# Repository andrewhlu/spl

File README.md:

<div class="center">
    
</div>

# Smart Parking Lot

A project for [ECE 189 - Computer Engineering Capstone](https://web.ece.ucsb.edu/~yoga/capstone/) led by Professor Isukapalli at UC Santa Barbara

---

[Parkingbase Demo Video](https://www.youtube.com/watch?v=abxjF7t0qpM)

[Parkingbase Poster](docs/poster.pdf)

---

## Team Members

* Andrew Lu
* Finn Linderman
* Luyao Han
* Seungjun Cho

## The Problem

Drivers spend too much time in parking lots trying to find an open space to park in. Many parking lots only have per-floor capacity indicators, and existing solutions are prohibitively expensive.

What if we could utilize low-cost sensors and a companion application to navigate drivers to empty parking spots faster, at a low cost to facility owners?

## Project Overview

**The goal of this project is to design a smart parking lot that will direct drivers to the nearest open parking space in an efficient, accurate, and clean manner.**

We accomplish this using:

* Small, inexpensive parking lot sensors with long-range and low-power transmission
* Modern, open-source, and cloud-based software solutions
* Easy-to-use mobile interfaces

# Technical Details

For a more detailed description, please take a look at our [project presentation slides](docs/final-presentation.pdf).

## System Overview

## Application Scene

## Block Diagram

<div class="center">
  
</div>

## Sensor Unit Assembly

<div class="center">

</div>

## Firmware Block Diagram

<div class="center">
  
</div>

## Sensor Unit PCB Design

The raw Kicad design files can be found in the [pcb-design folder](https://github.com/andrewhlu/spl/tree/main/pcb_design) in our repo.

[PCB Schematic (as PDF)](docs/sch.pdf)

[PCB Schematic (as PNG Image)](docs/sch.png)

## GUI Screenshots

Driver User Interface:

Editor User Interface:

## Code Repositories

* [spl](https://github.com/andrewhlu/spl)
  * Documentation for this website
  * PCB Design files
  * Demo pictures
* [spl-web](https://github.com/andrewhlu/spl-web)
  * Code for our website, including the React frontend and backend API routes
* [parkingbase-auth](https://github.com/andrewhlu/parkingbase-auth)
  * Code for our custom authentication server

# Project Progress Updates

[Initial Design](docs/initial-design.pdf)

[Milestone 1](docs/milestone1.pdf)

[Milestone 2](docs/milestone2.pdf)

[Fall Quarter Review Presentation](docs/fall-quarter-review.pdf)

[Winter Quarter Review Presentation](docs/winter-quarter-review.pdf)

[Final Poster](docs/poster.pdf)

[Final Presentation](docs/final-presentation.pdf)

<!-- Custom CSS for GitHub Pages -->

<style>
  .markdown-body h1:first-of-type {
    display: none;
  }

  .center {
    text-align: center;
    padding: 1rem;
  }
</style>

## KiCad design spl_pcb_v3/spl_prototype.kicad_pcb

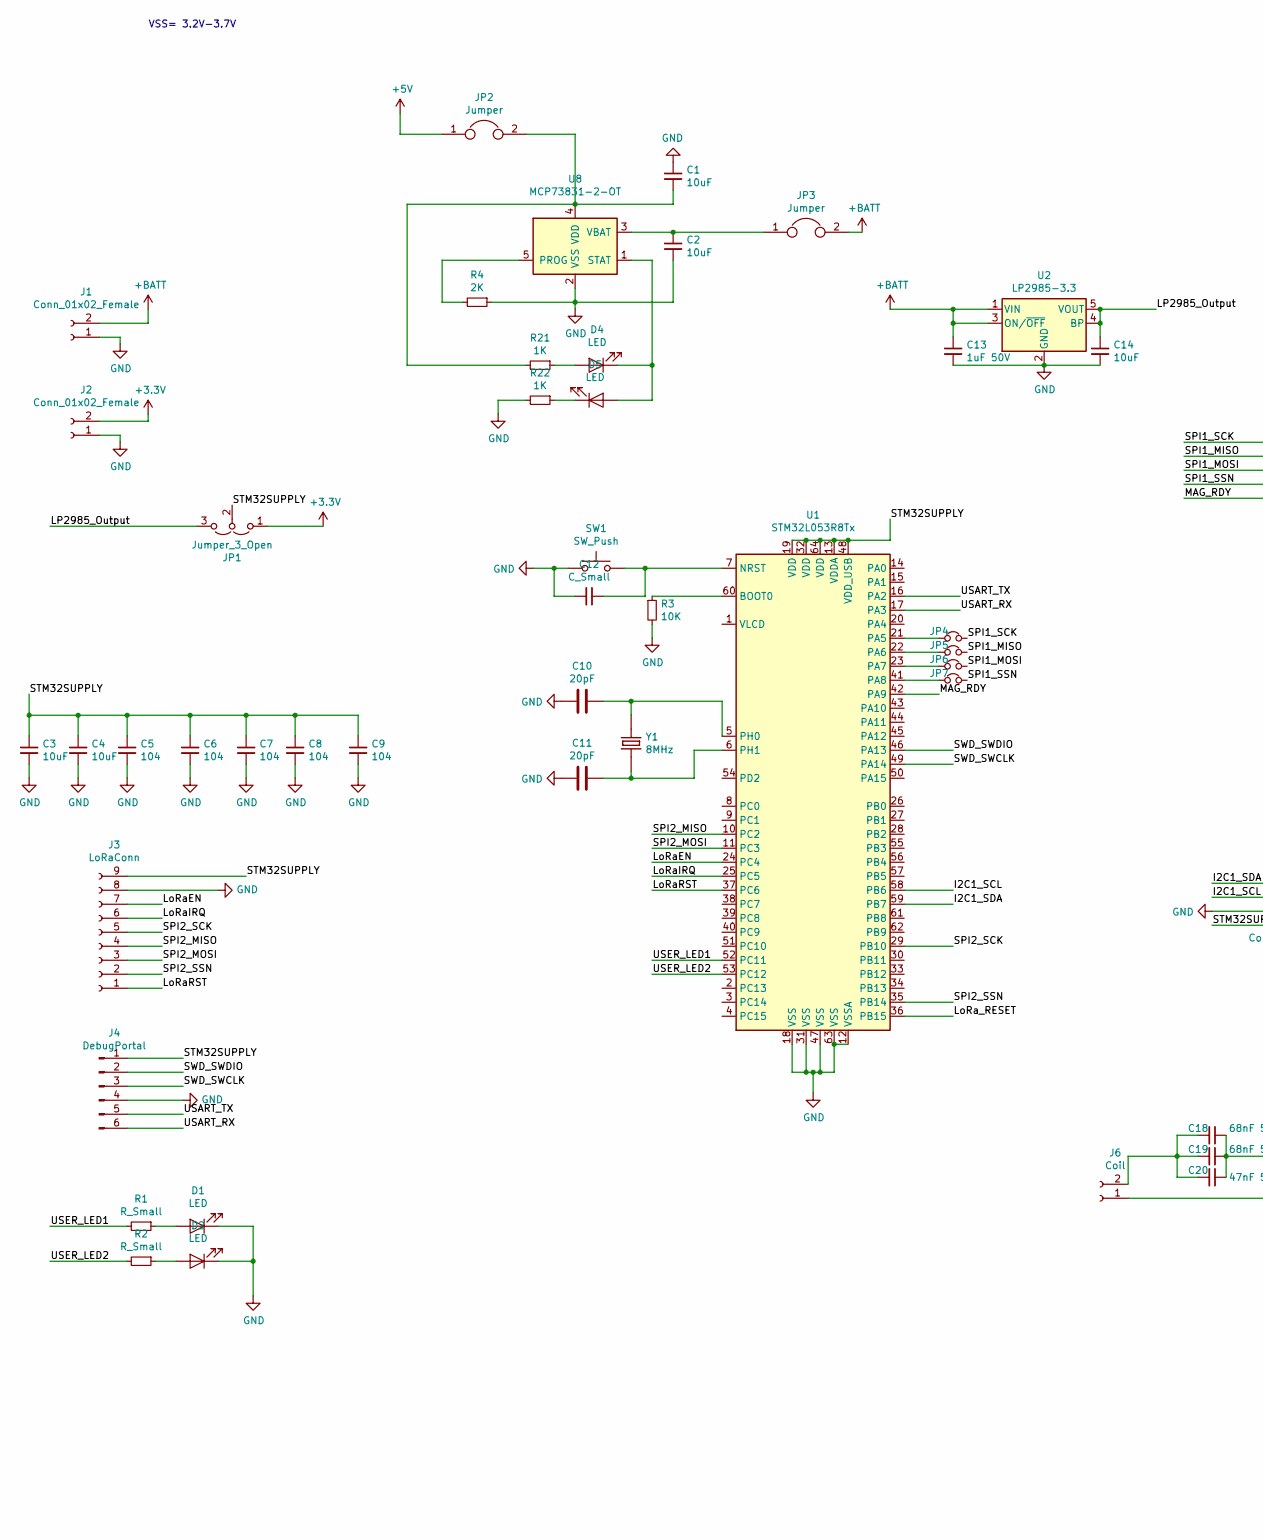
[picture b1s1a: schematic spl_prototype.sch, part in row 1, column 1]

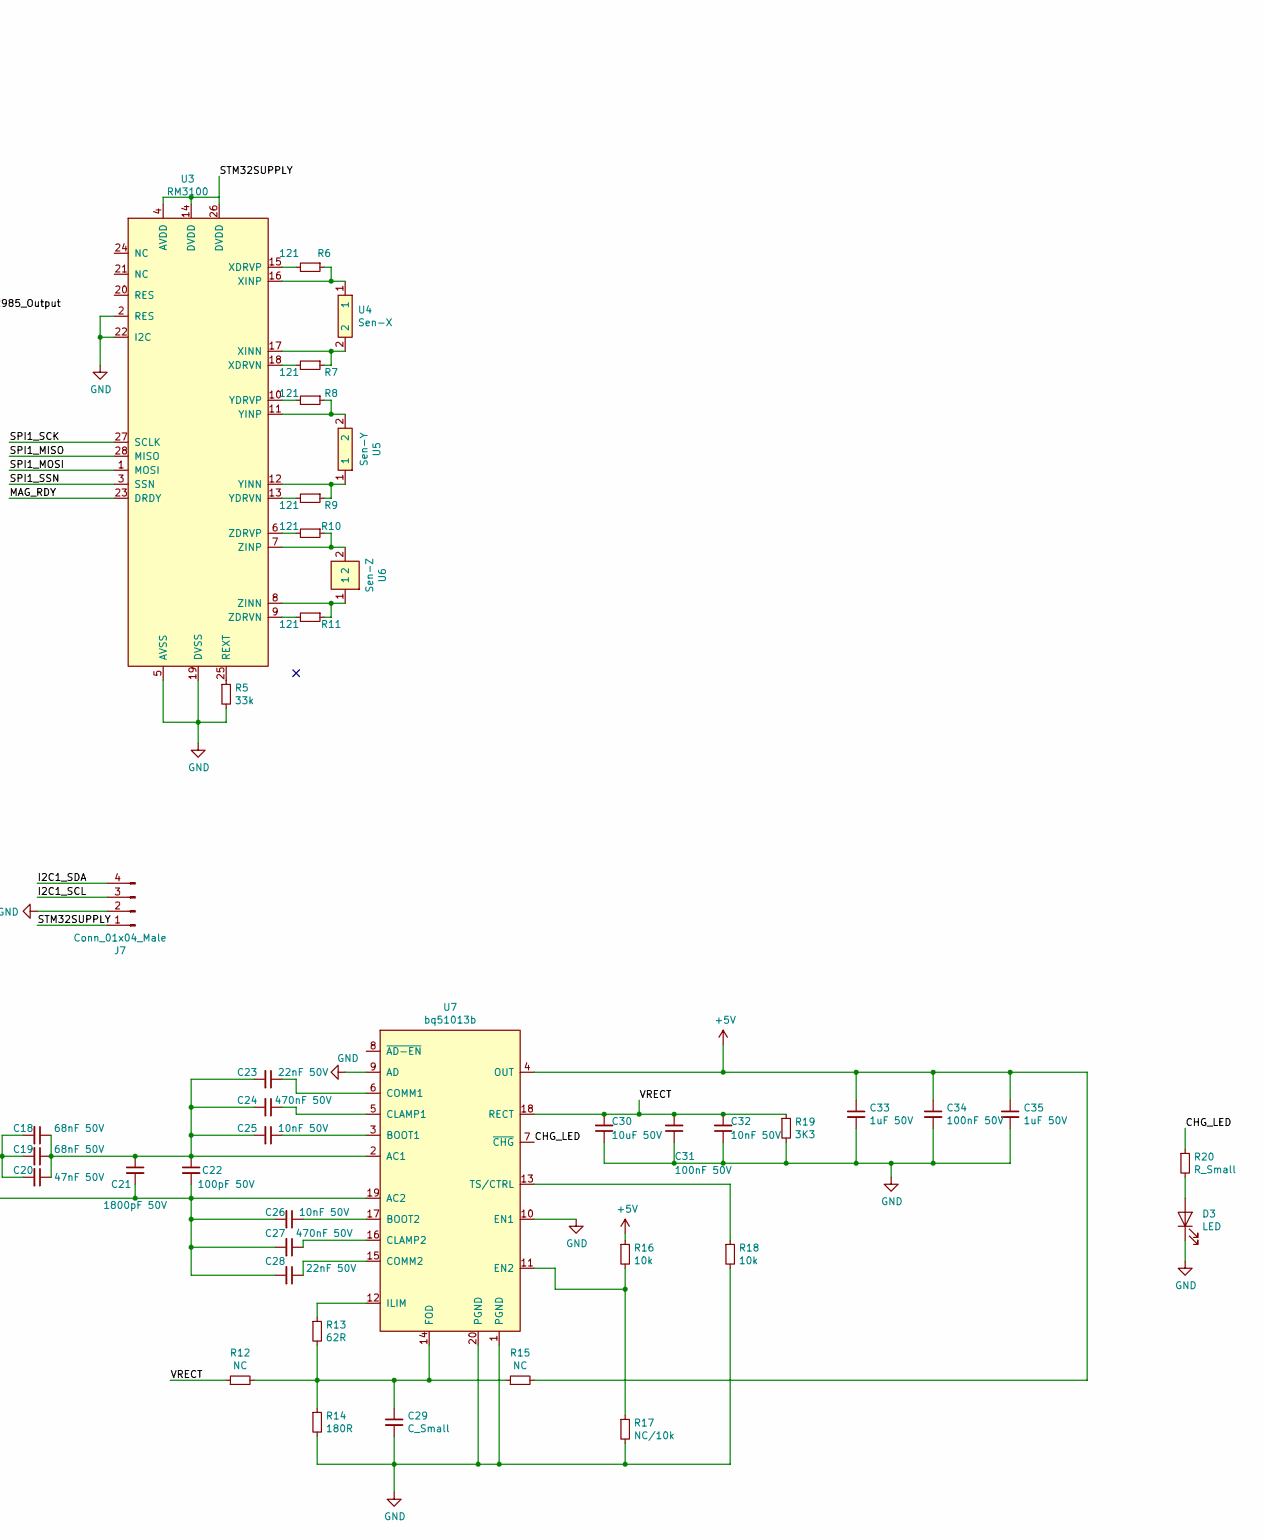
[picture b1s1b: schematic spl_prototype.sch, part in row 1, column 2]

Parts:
C1, C2, C3, C4, C14: 10uF; C_0603_1608Metric_Pad1.05x0.95mm_HandSolder
C5, C6, C7, C8, C9: 104; C_0603_1608Metric_Pad1.05x0.95mm_HandSolder
C10, C11: 20pF; C_0603_1608Metric_Pad1.05x0.95mm_HandSolder
C12, C29: C_Small; C_0603_1608Metric_Pad1.05x0.95mm_HandSolder
C13, C33, C35: 1uF 50V; C_0603_1608Metric_Pad1.05x0.95mm_HandSolder
C18, C19: 68nF 50V; C_0603_1608Metric_Pad1.05x0.95mm_HandSolder
C20: 47nF 50V; C_0603_1608Metric_Pad1.05x0.95mm_HandSolder
C21: 1800pF 50V; C_0603_1608Metric_Pad1.05x0.95mm_HandSolder
C22: 100pF 50V; C_0603_1608Metric_Pad1.05x0.95mm_HandSolder
C23, C28: 22nF 50V; C_0603_1608Metric_Pad1.05x0.95mm_HandSolder
C24, C27: 470nF 50V; C_0603_1608Metric_Pad1.05x0.95mm_HandSolder
C25, C26, C32: 10nF 50V; C_0603_1608Metric_Pad1.05x0.95mm_HandSolder
C30: 10uF 50V; C_0603_1608Metric_Pad1.05x0.95mm_HandSolder
C31, C34: 100nF 50V; C_0603_1608Metric_Pad1.05x0.95mm_HandSolder
D1, D2, D3, D4, D5: LED; LED_0603_1608Metric_Pad1.05x0.95mm_HandSolder
J1, J2: Conn_01x02_Female; JST_EH_B2B-EH-A_1x02_P2.50mm_Vertical
J3: LoRaConn; PinSocket_1x09_P2.54mm_Vertical
J4: DebugPortal; PinHeader_1x06_P2.54mm_Vertical
J6: Coil; R_Axial_DIN0204_L3.6mm_D1.6mm_P5.08mm_Horizontal
J7: Conn_01x04_Male; PinHeader_1x04_P2.54mm_Vertical
JP1: Jumper_3_Open; SolderJumper-3_P1.3mm_Open_Pad1.0x1.5mm
JP2, JP3: Jumper; SolderJumper-2_P1.3mm_Open_Pad1.0x1.5mm
JP4, JP5, JP6, JP7: Jumper_NC_Small; PinHeader_1x02_P2.54mm_Vertical
R1, R2, R20: R_Small; R_0603_1608Metric_Pad1.05x0.95mm_HandSolder
R3: 10K; R_0603_1608Metric_Pad1.05x0.95mm_HandSolder
R4: 2K; R_0603_1608Metric_Pad1.05x0.95mm_HandSolder
R5: 33k; R_0603_1608Metric_Pad1.05x0.95mm_HandSolder
R6, R7, R8, R9, R10, R11: 121; R_0603_1608Metric_Pad1.05x0.95mm_HandSolder
R12, R15: NC; R_0603_1608Metric_Pad1.05x0.95mm_HandSolder
R13: 62R; R_0603_1608Metric_Pad1.05x0.95mm_HandSolder
R14: 180R; R_0603_1608Metric_Pad1.05x0.95mm_HandSolder
R16, R18: 10k; R_0603_1608Metric_Pad1.05x0.95mm_HandSolder
R17: NC/10k; R_0603_1608Metric_Pad1.05x0.95mm_HandSolder
R19: 3K3; R_0603_1608Metric_Pad1.05x0.95mm_HandSolder
R21, R22: 1K; R_0603_1608Metric_Pad1.05x0.95mm_HandSolder
SW1: SW_Push; SW_SPST_B3U-1000P
U1: STM32L053R8Tx; LQFP-64_10x10mm_P0.5mm
U2: LP2985-3.3; SOT-23-5
U3: RM3100; QFN-28_EP_4x4_Pitch0.4mm
U4: Sen-X; RM3100_SEN_XY
U5: Sen-Y; RM3100_SEN_XY
U6: Sen-Z; RM3100_SEN_Z
U7: bq51013b; VQFN20
U8: MCP73831-2-OT; SOT-23-5
Y1: 8MHz; XTAL_ECS-80-18-10X; PARTREV 2017

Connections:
+3V3: J2.2, JP1.1 (A)
+5V: C33.1, C34.1, C35.1, JP2.1, R15.2, R16.1, U7.4 (OUT)
+BATT: C13.1, J1.2, JP3.2, U2.1 (VIN), U2.3 (ON/~OFF~)
/CHG_LED: R20.1, U7.7 (~CHG)
/I2C1_SCL: J7.3, U1.58 (PB6)
/I2C1_SDA: J7.4, U1.59 (PB7)
/LP2985_Output: C14.1, JP1.3 (B), U2.4 (BP), U2.5 (VOUT)
/LoRaEN: J3.7, U1.24 (PC4)
/LoRaIRQ: J3.6, U1.25 (PC5)
/LoRaRST: J3.1, U1.37 (PC6)
/LoRa_RESET: U1.36 (PB15)
/MAG_RDY: U1.42 (PA9), U3.23 (DRDY)
/SPI1_MISO: JP5.1, JP5.2, U1.22 (PA6), U3.28 (MISO)
/SPI1_MOSI: JP6.1, JP6.2, U1.23 (PA7), U3.1 (MOSI)
/SPI1_SCK: JP4.1, JP4.2, U1.21 (PA5), U3.27 (SCLK)
/SPI1_SSN: JP7.1, JP7.2, U1.41 (PA8), U3.3 (SSN)
/SPI2_MISO: J3.4, U1.10 (PC2)
/SPI2_MOSI: J3.3, U1.11 (PC3)
/SPI2_SSN: J3.2, U1.35 (PB14)
/STM32SUPPLY: C3.1, C4.1, C5.1, C6.1, C7.1, C8.1, C9.1, J3.9, J4.1, J7.1, JP1.2 (C), U1.13 (VDDA), U1.19 (VDD), U1.32 (VDD), U1.48 (VDD_USB), U1.64 (VDD), U3.4 (AVDD), U3.14 (DVDD), U3.26 (DVDD)
/SWD_SWCLK: J4.3, U1.49 (PA14)
/SWD_SWDIO: J4.2, U1.46 (PA13)
/USART_RX: J4.6, U1.17 (PA3)
/USART_TX: J4.5, U1.16 (PA2)
/USER_LED1: R1.2, U1.52 (PC11)
/USER_LED2: R2.2, U1.53 (PC12)
/VRECT: C30.2, C31.2, C32.2, R12.1, R19.1, U7.18 (RECT)
GND: C1.1, C2.2, C3.2, C4.2, C5.2, C6.2, C7.2, C8.2, C9.2, C10.2, C11.2, C12.2, C13.2, C14.2, C29.2, C30.1, C31.1, C32.1, C33.2, C34.2, C35.2, D1.1 (K), D2.1 (K), D3.1 (K), J1.1, J2.1, J3.8, J4.4, J7.2, R3.2, R4.1, R5.2, R14.2, R17.2, R18.2, R19.2, R22.2, SW1.1, U1.12 (VSSA), U1.18 (VSS), U1.31 (VSS), U1.47 (VSS), U1.63 (VSS), U2.2 (GND), U3.2 (RES), U3.5 (AVSS), U3.19 (DVSS), U3.22 (I2C), U7.1 (PGND), U7.9 (AD), U7.10 (EN1), U7.20 (PGND), U8.2 (VSS)
unnamed: C1.2, JP2.2, R21.2, U8.4 (VDD)
unnamed: C2.1, JP3.1, U8.3 (VBAT)
unnamed: C10.1, U1.5 (PH0), Y1.1
unnamed: C11.1, U1.6 (PH1), Y1.2
unnamed: C12.1, SW1.2, U1.7 (NRST)
unnamed: C18.1, C19.1, C20.1, C21.1, C22.1, C23.2, C24.2, C25.2, U7.2 (AC1)
unnamed: C18.2, C19.2, C20.2, J6.2
unnamed: C21.2, C22.2, C26.2, C27.2, C28.2, J6.1, U7.19 (AC2)
unnamed: C23.1, U7.6 (COMM1)
unnamed: C24.1, U7.5 (CLAMP1)
unnamed: C25.1, U7.3 (BOOT1)
unnamed: C26.1, U7.17 (BOOT2)
unnamed: C27.1, U7.16 (CLAMP2)
unnamed: C28.1, U7.15 (COMM2)
unnamed: C29.1, R12.2, R13.2, R14.1, R15.1, U7.14 (FOD)
unnamed: D1.2 (A), R1.1
unnamed: D2.2 (A), R2.1
unnamed: D3.2 (A), R20.2
unnamed: D4.1 (K), D5.2 (A), U8.1 (STAT)
unnamed: D4.2 (A), R21.1
unnamed: D5.1 (K), R22.1
unnamed: R3.1, U1.60 (BOOT0)
unnamed: R4.2, U8.5 (PROG)
unnamed: R5.1, U3.25 (REXT)
unnamed: R6.1, U3.16 (XINP), U4.1
unnamed: R6.2, U3.15 (XDRVP)
unnamed: R7.1, U3.17 (XINN), U4.2
unnamed: R7.2, U3.18 (XDRVN)
unnamed: R8.1, U3.11 (YINP), U5.2
unnamed: R8.2, U3.10 (YDRVP)
unnamed: R9.1, U3.12 (YINN), U5.1
unnamed: R9.2, U3.13 (YDRVN)
unnamed: R10.1, U3.7 (ZINP), U6.2
unnamed: R10.2, U3.6 (ZDRVP)
unnamed: R11.1, U3.8 (ZINN), U6.1
unnamed: R11.2, U3.9 (ZDRVN)
unnamed: R13.1, U7.12 (ILIM)
unnamed: R16.2, R17.1, U7.11 (EN2)
unnamed: R18.1, U7.13 (TS/CTRL)

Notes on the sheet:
VSS= 3.2V-3.7V

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
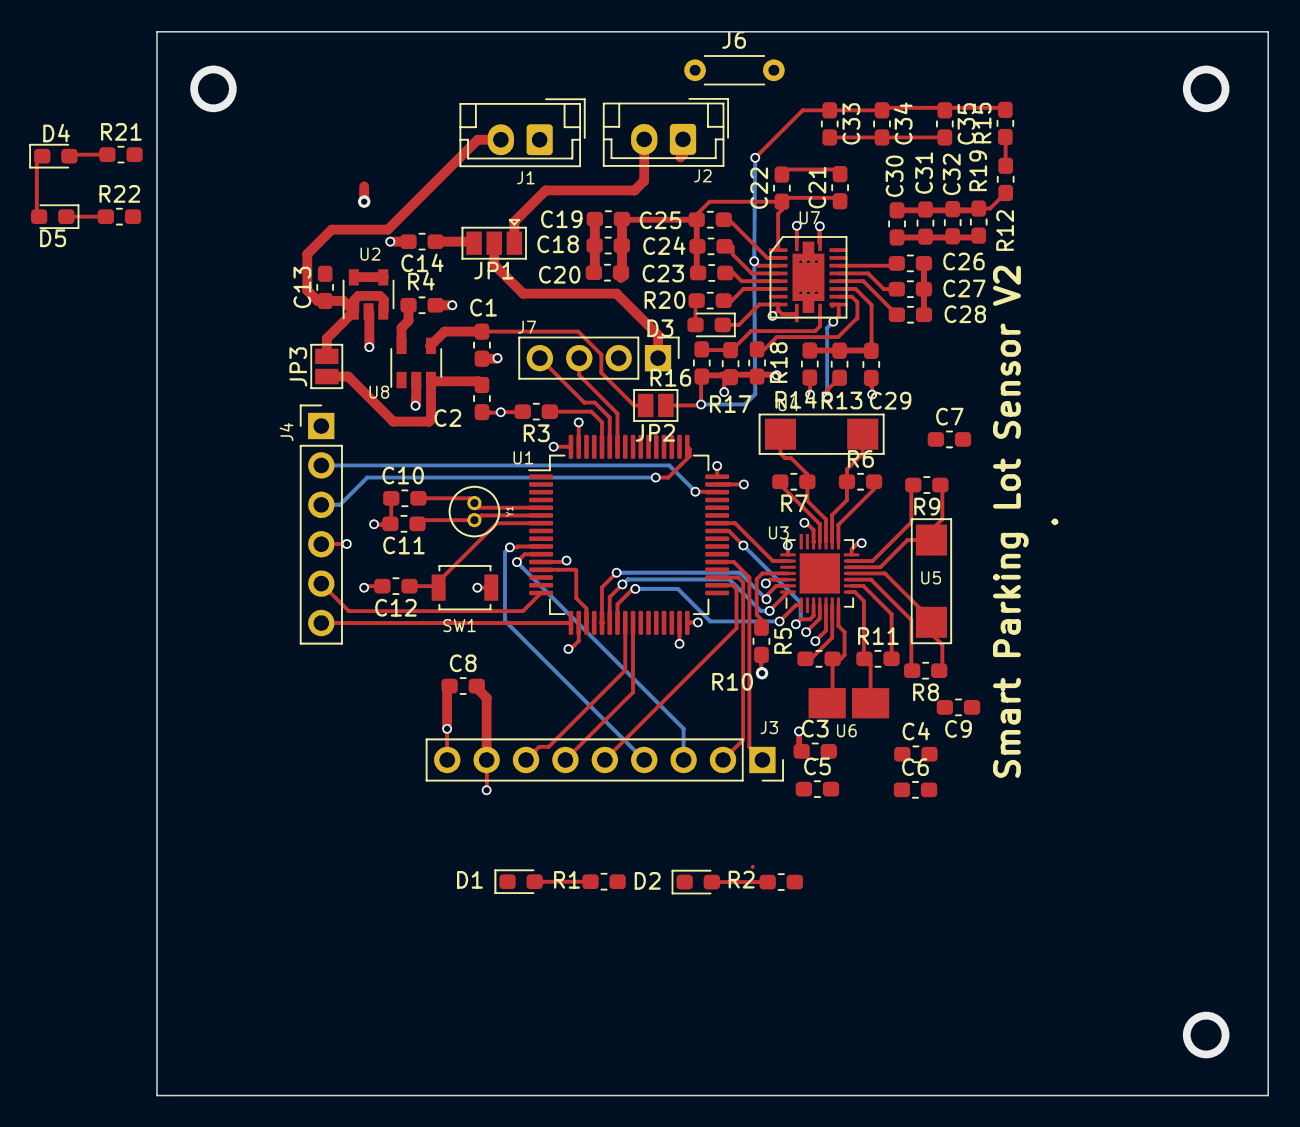
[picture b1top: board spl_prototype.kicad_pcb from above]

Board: 4 copper layers, 71.6 x 68.6 mm, 78 parts (0 on the bottom side), 67 nets.

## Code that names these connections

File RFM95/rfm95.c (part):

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		HAL_GPIO_WritePin(GPIOB, GPIO_PIN_13, GPIO_PIN_RESET);
}

//MOSI PA7 
void SPI_MOSI_1(){
		HAL_GPIO_WritePin(GPIOC, GPIO_PIN_3, GPIO_PIN_SET);
}
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}


//MISO PA6 
uint8_t SPI_READ_MISO(){
		GPIO_PinState bitstatus = HAL_GPIO_ReadPin(GPIOC, GPIO_PIN_2);
	return bitstatus;
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{
   GPIO_InitTypeDef GPIO_InitStruct = {0};
	
	//Configure GPIO pins : PC3, PC4, PC6
  GPIO_InitStruct.Pin = GPIO_PIN_3 | GPIO_PIN_4 | GPIO_PIN_6;
  GPIO_InitStruct.Mode = GPIO_MODE_OUTPUT_PP;
  GPIO_InitStruct.Pull = GPIO_NOPULL;
  GPIO_InitStruct.Speed = GPIO_SPEED_FREQ_HIGH;
  HAL_GPIO_Init(GPIOC, &GPIO_InitStruct);
	 
	//Configure GPIO pins : PB13, 14,15
  GPIO_InitStruct.Pin = GPIO_PIN_13 | GPIO_PIN_14 | GPIO_PIN_15;
  GPIO_InitStruct.Mode = GPIO_MODE_OUTPUT_PP;
  GPIO_InitStruct.Pull = GPIO_NOPULL;
  GPIO_InitStruct.Speed = GPIO_SPEED_FREQ_HIGH;
  HAL_GPIO_Init(GPIOB, &GPIO_InitStruct);
	 
	//PC2, PC5
	GPIO_InitStruct.Pin = GPIO_PIN_2 | GPIO_PIN_5;
  GPIO_InitStruct.Mode = GPIO_MODE_INPUT;
  GPIO_InitStruct.Pull = GPIO_NOPULL;
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
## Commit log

2020-10-02 Add initial project description
2020-10-02 Add team members and relevant links
2020-10-07 10/5 Notes
2020-10-07 Add on to 10/5 notes
2020-10-09 Add notes for 10/9 meeting
2020-10-28 Add new meeting notes and Milestone 1, move meeting notes to new page
2020-10-28 Fix page title and milestone link
2020-10-28 Add parts list
2020-10-29 Update LoRa and Zigbee order destinations
2020-11-06 Update budget sheet
2021-03-15 luyao sync
2021-03-30 sync
2021-03-30 uploaded PCB V2. Kicad
2021-05-24 Updated ReadMe with some stub for GUI and Gateway
    Waiting on assets/photos and will add these when I get them. Will download available assets from the slides/poster
2021-05-24 added new photos
2021-05-24 Added Photos
    Added two new photos
2021-05-25 added logo
2021-05-25 Added Logo
    Added the parking base logo
2021-05-25 Fixed Logo
2021-05-25 added block diagram
2021-05-25 Updated the Block Diagram
2021-05-25 Text changes
2021-05-25 added a new unit
2021-05-25 Updated sensor unit image
2021-05-29 updated relative path for libs
2021-06-04 AL - Major website edits
2021-06-04 AL - Hide initial spl header
2021-06-04 AL - Remove duplicate file
2021-06-04 AL - Remove empty markdown file
